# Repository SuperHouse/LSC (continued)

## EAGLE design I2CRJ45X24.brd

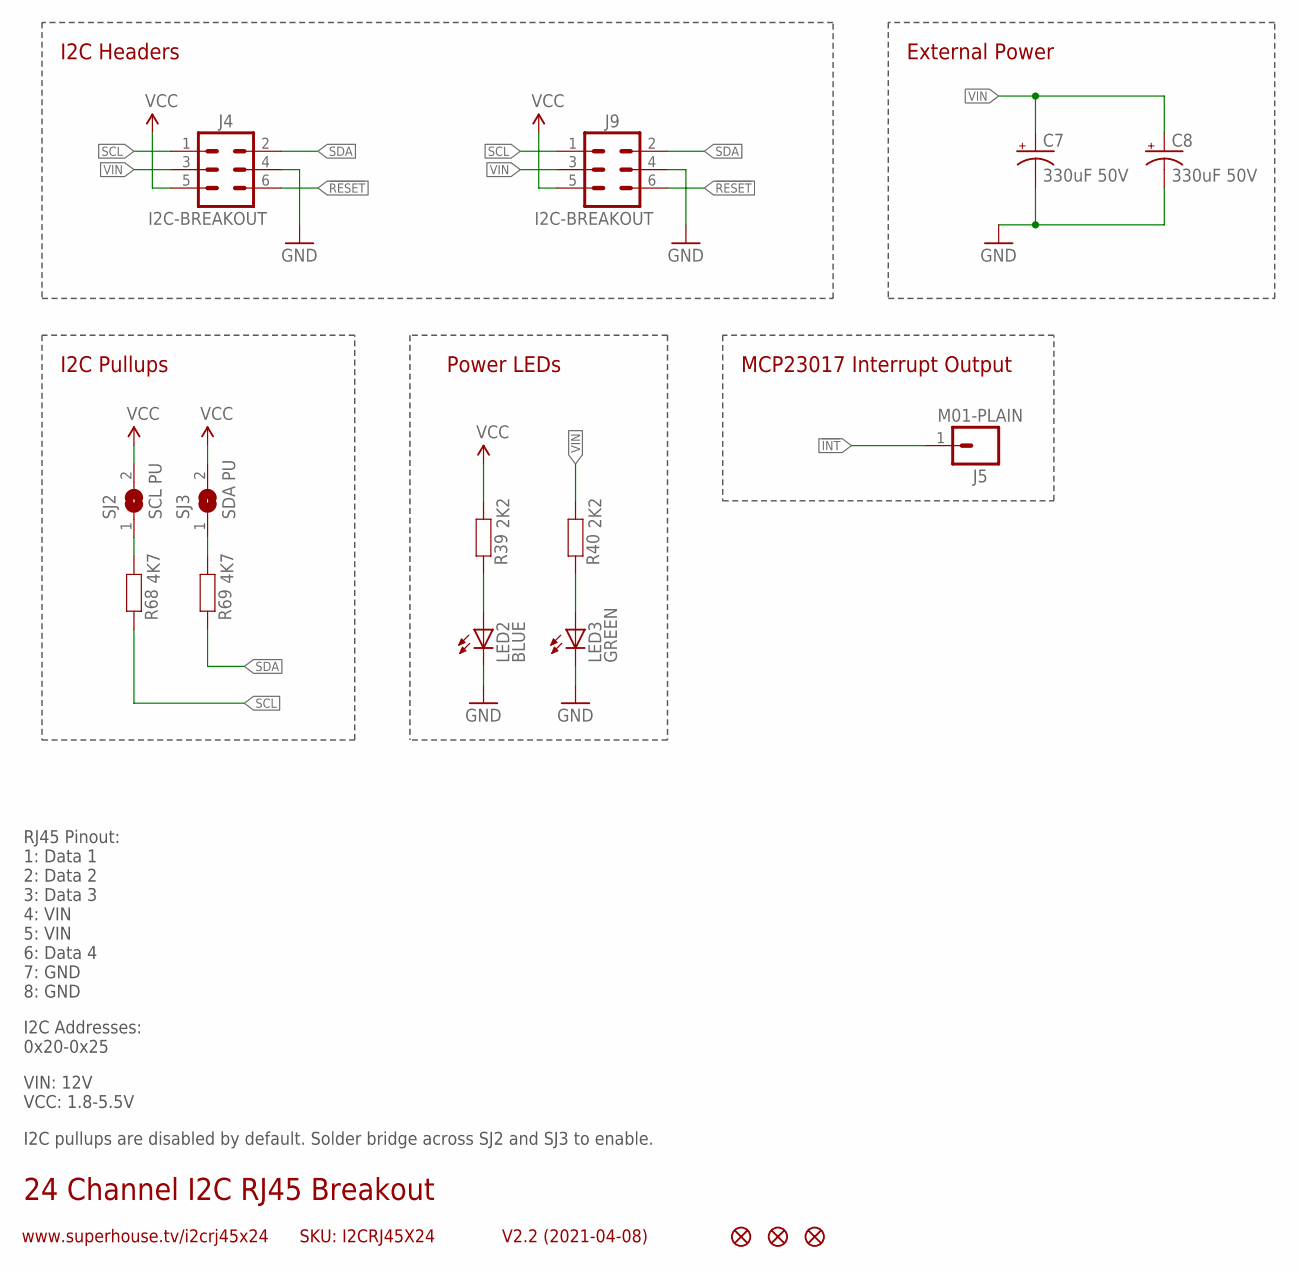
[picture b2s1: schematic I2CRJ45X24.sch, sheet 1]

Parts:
C7, C8: 330uF 50V; PANASONIC_G
FID1, FID2, FID3: FIDUCIAL1X2.5; FIDUCIAL-1X2.5
J4, J9: I2C-BREAKOUT; 2X03-SHROUDED
J5: M01-PLAIN; 1X01
LED2: BLUE; LED-0603
LED3: GREEN; LED-0603
R39, R40: 2K2; R0603
R68, R69: 4K7; R0603
SJ2: SCL PU; SJ
SJ3: SDA PU; SJ

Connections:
!INT: J5.1; also elsewhere on the board
!RESET: J4.6, J9.6; also elsewhere on the board
GND: C7.-, C8.-, J4.4, J9.4, LED2.C, LED3.C; also elsewhere on the board
unnamed: R68.2, SJ2.1
unnamed: R69.2, SJ3.1
unnamed: LED2.A, R39.1
unnamed: LED3.A, R40.1
SCL: J4.1, J9.1, R68.1; also elsewhere on the board
SDA: J4.2, J9.2, R69.1; also elsewhere on the board
VCC: J4.5, J9.5, R39.2, SJ2.2, SJ3.2; also elsewhere on the board
VIN: C7.+, C8.+, J4.3, J9.3, R40.2; also elsewhere on the board

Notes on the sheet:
24 Channel I2C RJ45 Breakout
V2.2 (2021-04-08)
www.superhouse.tv/i2crj45x24
SKU: I2CRJ45X24
RJ45 Pinout: 1: Data 1 2: Data 2 3: Data 3 4: VIN 5: VIN 6: Data 4 7: GND 8: GND
VIN: 12V VCC: 1.8-5.5V
I2C Addresses: 0x20-0x25
External Power
I2C Headers
MCP23017 Interrupt Output
I2C Pullups
I2C pullups are disabled by default. Solder bridge across SJ2 and SJ3 to enable.
Power LEDs

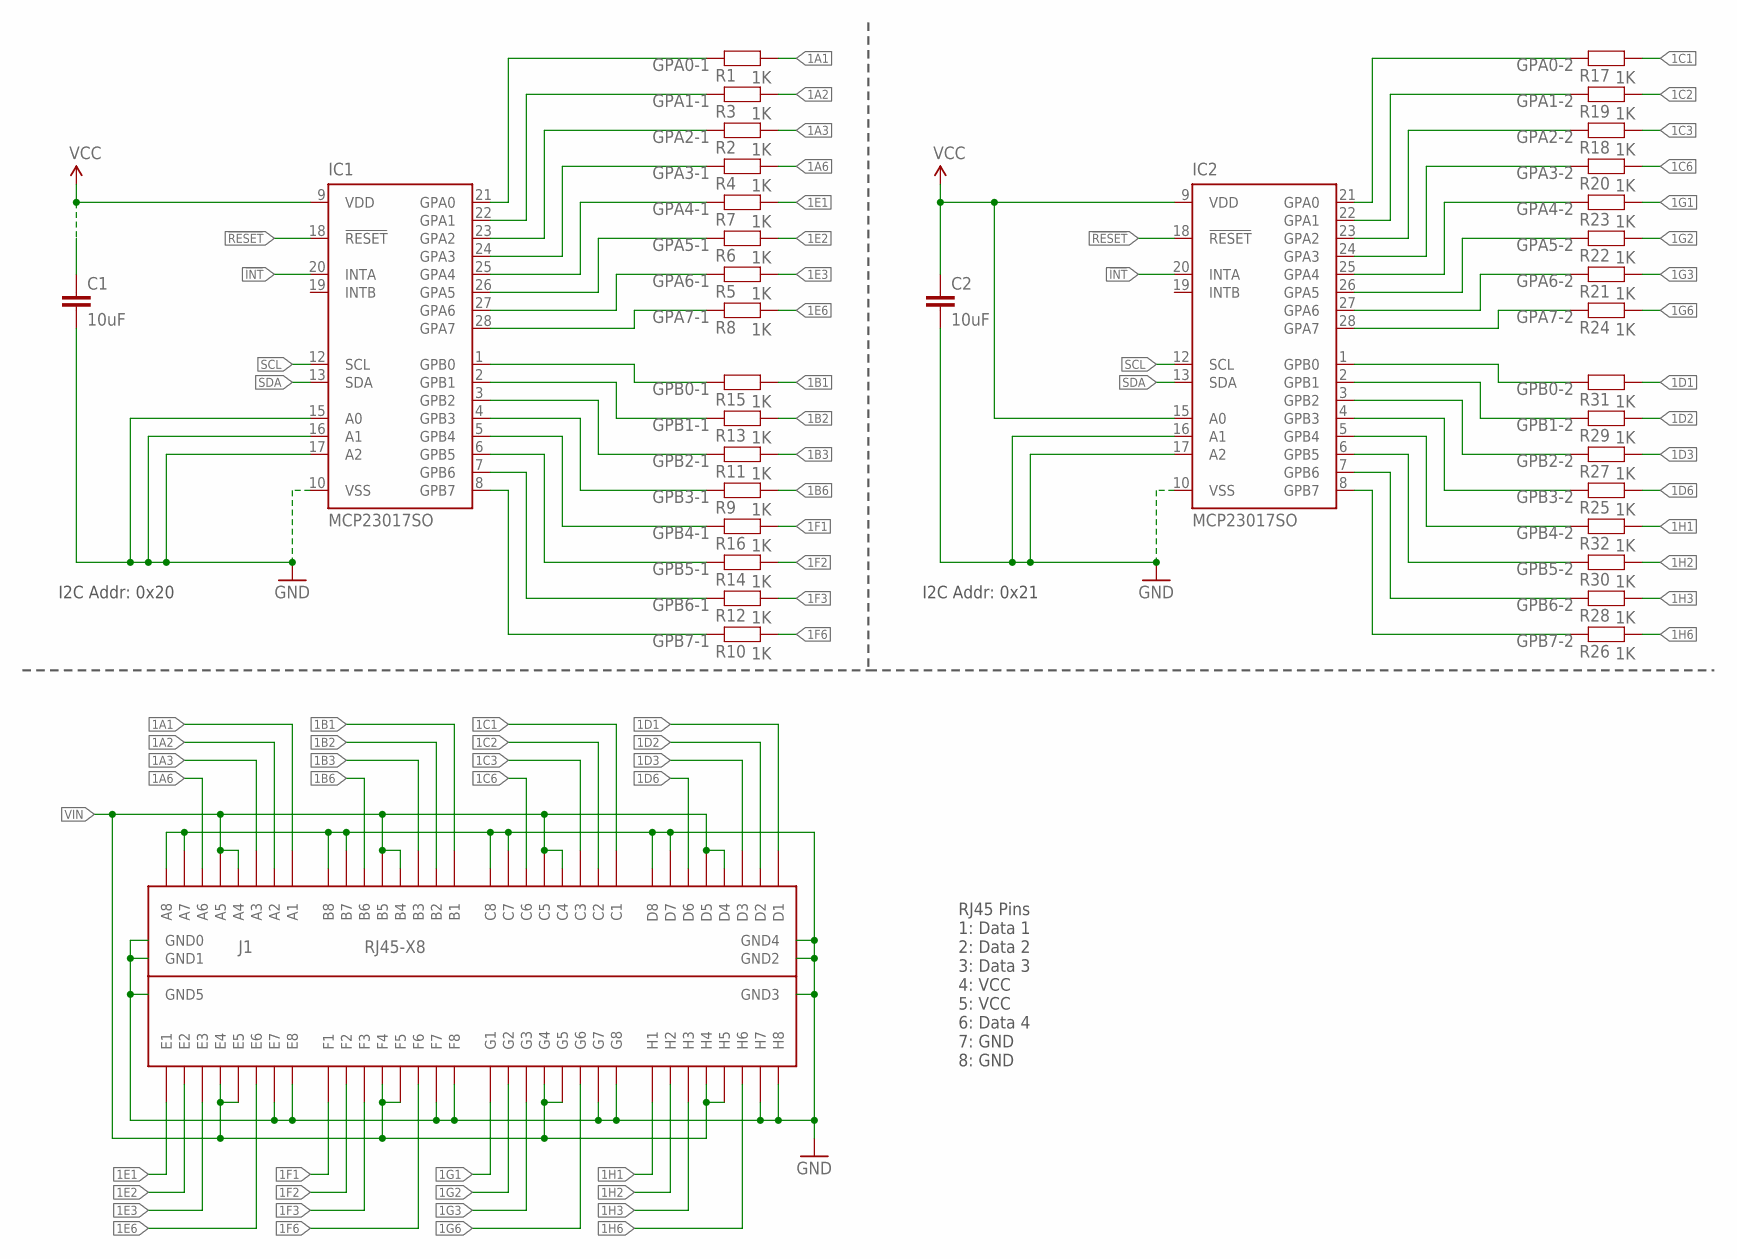
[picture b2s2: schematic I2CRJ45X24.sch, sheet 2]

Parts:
C1, C2: 10uF; C0805
IC1, IC2: MCP23017SO; SO28W
J1: RJ45-X8; RJ45-2X4
R1, R2, R3, R4, R5, R6, R7, R8, R9, R10, R11, R12, R13, R14, R15, R16, R17, R18, R19, R20, R21, R22, R23, R24, R25, R26, R27, R28, R29, R30, R31, R32: 1K; R0603

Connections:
1A1: J1.A1, R1.2
1A2: J1.A2, R3.2
1A3: J1.A3, R2.2
1A6: J1.A6, R4.2
1B1: J1.B1, R15.2
1B2: J1.B2, R13.2
1B3: J1.B3, R11.2
1B6: J1.B6, R9.2
1C1: J1.C1, R17.2
1C2: J1.C2, R19.2
1C3: J1.C3, R18.2
1C6: J1.C6, R20.2
1D1: J1.D1, R31.2
1D2: J1.D2, R29.2
1D3: J1.D3, R27.2
1D6: J1.D6, R25.2
1E1: J1.E1, R7.2
1E2: J1.E2, R6.2
1E3: J1.E3, R5.2
1E6: J1.E6, R8.2
1F1: J1.F1, R16.2
1F2: J1.F2, R14.2
1F3: J1.F3, R12.2
1F6: J1.F6, R10.2
1G1: J1.G1, R23.2
1G2: J1.G2, R22.2
1G3: J1.G3, R21.2
1G6: J1.G6, R24.2
1H1: J1.H1, R32.2
1H2: J1.H2, R30.2
1H3: J1.H3, R28.2
1H6: J1.H6, R26.2
!INT: IC1.20 (INTA), IC2.20 (INTA); also elsewhere on the board
!RESET: IC1.18 (!RESET), IC2.18 (!RESET); also elsewhere on the board
GND: C1.2, C2.2, IC1.10 (VSS), IC1.15 (A0), IC1.16 (A1), IC1.17 (A2), IC2.10 (VSS), IC2.16 (A1), IC2.17 (A2), J1.A7, J1.A8, J1.B7, J1.B8, J1.C7, J1.C8, J1.D7, J1.D8, J1.E7, J1.E8, J1.F7, J1.F8, J1.G7, J1.G8, J1.GND0, J1.GND1, J1.GND2, J1.GND3, J1.GND4, J1.GND5, J1.H7, J1.H8; also elsewhere on the board
GPA0-1: IC1.21 (GPA0), R1.1
GPA0-2: IC2.21 (GPA0), R17.1
GPA1-1: IC1.22 (GPA1), R3.1
GPA1-2: IC2.22 (GPA1), R19.1
GPA2-1: IC1.23 (GPA2), R2.1
GPA2-2: IC2.23 (GPA2), R18.1
GPA3-1: IC1.24 (GPA3), R4.1
GPA3-2: IC2.24 (GPA3), R20.1
GPA4-1: IC1.25 (GPA4), R7.1
GPA4-2: IC2.25 (GPA4), R23.1
GPA5-1: IC1.26 (GPA5), R6.1
GPA5-2: IC2.26 (GPA5), R22.1
GPA6-1: IC1.27 (GPA6), R5.1
GPA6-2: IC2.27 (GPA6), R21.1
GPA7-1: IC1.28 (GPA7), R8.1
GPA7-2: IC2.28 (GPA7), R24.1
GPB0-1: IC1.1 (GPB0), R15.1
GPB0-2: IC2.1 (GPB0), R31.1
GPB1-1: IC1.2 (GPB1), R13.1
GPB1-2: IC2.2 (GPB1), R29.1
GPB2-1: IC1.3 (GPB2), R11.1
GPB2-2: IC2.3 (GPB2), R27.1
GPB3-1: IC1.4 (GPB3), R9.1
GPB3-2: IC2.4 (GPB3), R25.1
GPB4-1: IC1.5 (GPB4), R16.1
GPB4-2: IC2.5 (GPB4), R32.1
GPB5-1: IC1.6 (GPB5), R14.1
GPB5-2: IC2.6 (GPB5), R30.1
GPB6-1: IC1.7 (GPB6), R12.1
GPB6-2: IC2.7 (GPB6), R28.1
GPB7-1: IC1.8 (GPB7), R10.1
GPB7-2: IC2.8 (GPB7), R26.1
SCL: IC1.12 (SCL), IC2.12 (SCL); also elsewhere on the board
SDA: IC1.13 (SDA), IC2.13 (SDA); also elsewhere on the board
VCC: C1.1, C2.1, IC1.9 (VDD), IC2.9 (VDD), IC2.15 (A0); also elsewhere on the board
VIN: J1.A4, J1.A5, J1.B4, J1.B5, J1.C4, J1.C5, J1.D4, J1.D5, J1.E4, J1.E5, J1.F4, J1.F5, J1.G4, J1.G5, J1.H4, J1.H5; also elsewhere on the board

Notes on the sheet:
RJ45 Pins 1: Data 1 2: Data 2 3: Data 3 4: VCC 5: VCC 6: Data 4 7: GND 8: GND
I2C Addr: 0x20
I2C Addr: 0x21

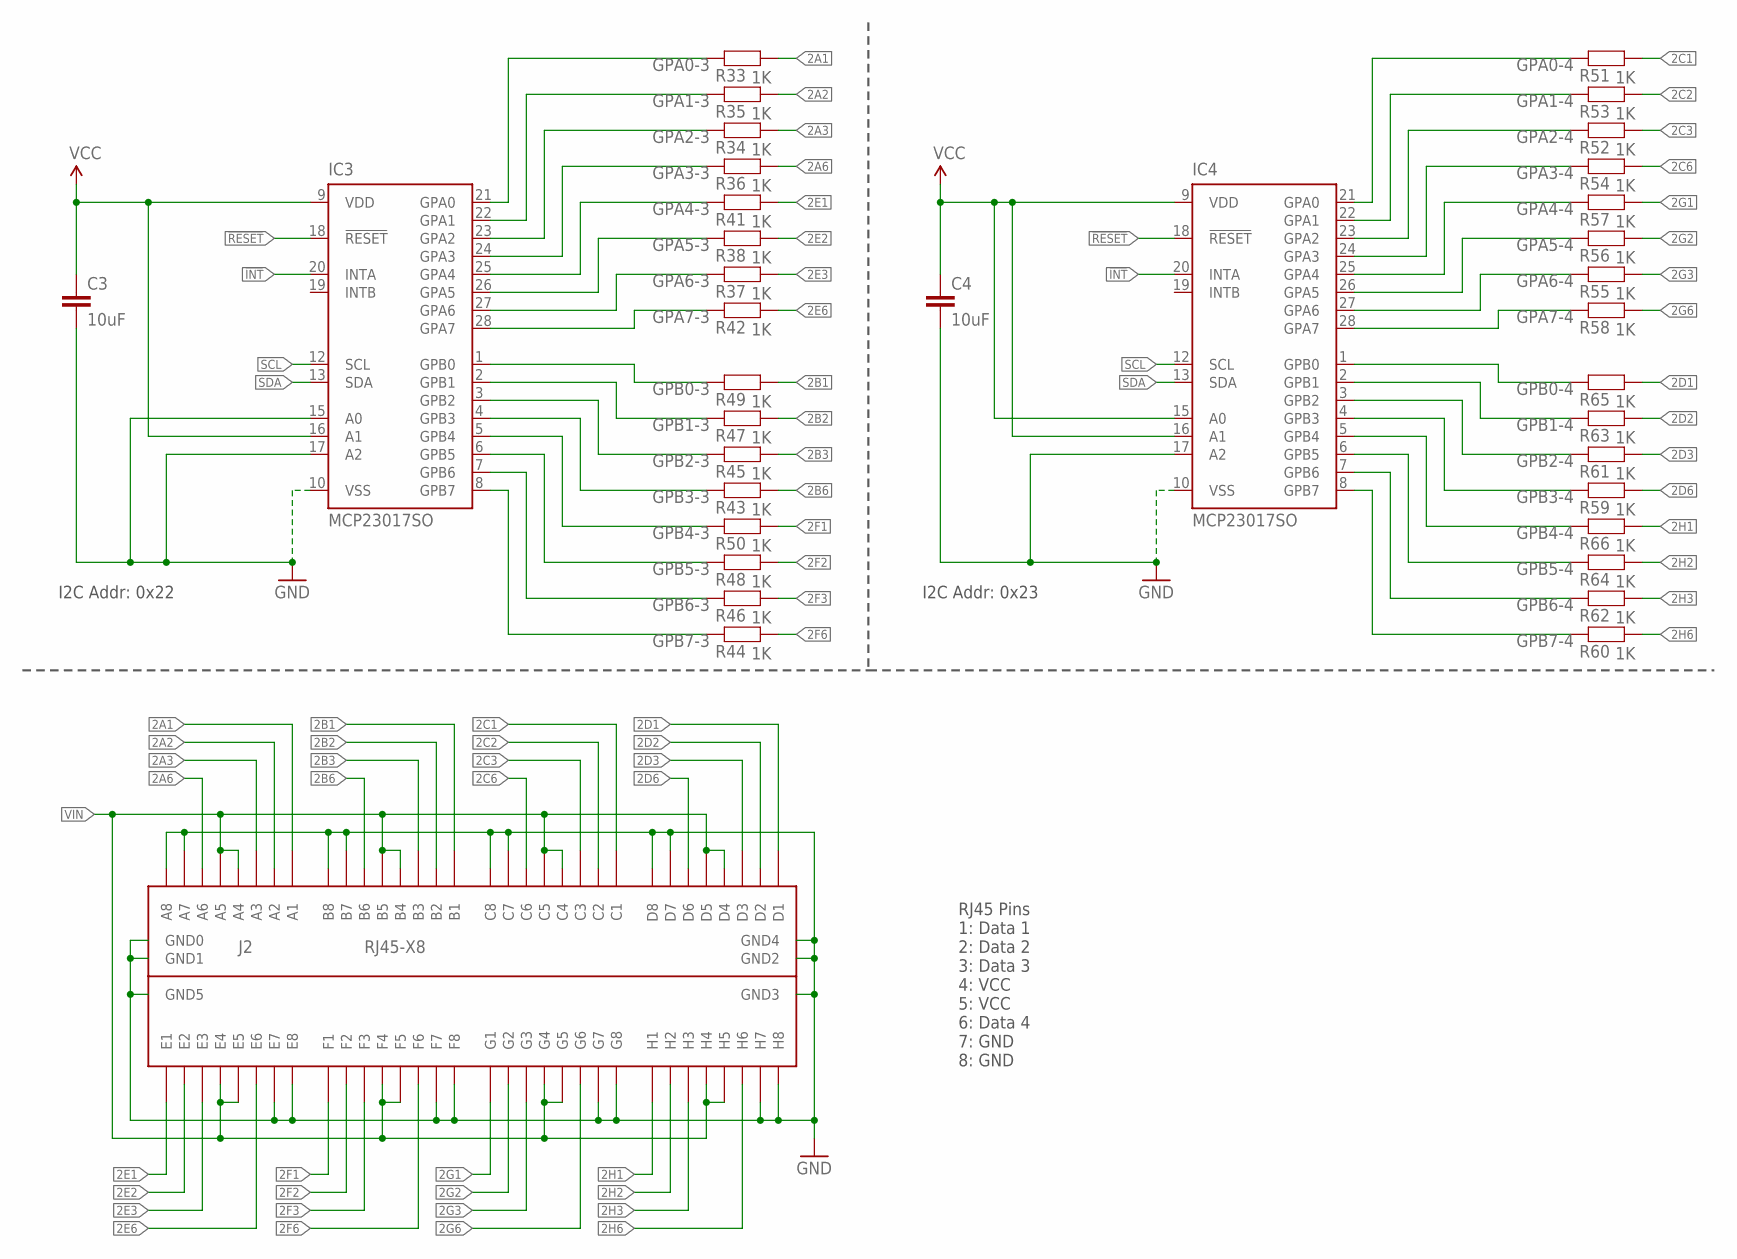
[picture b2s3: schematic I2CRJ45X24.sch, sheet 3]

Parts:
C3, C4: 10uF; C0805
IC3, IC4: MCP23017SO; SO28W
J2: RJ45-X8; RJ45-2X4
R33, R34, R35, R36, R37, R38, R41, R42, R43, R44, R45, R46, R47, R48, R49, R50, R51, R52, R53, R54, R55, R56, R57, R58, R59, R60, R61, R62, R63, R64, R65, R66: 1K; R0603

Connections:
2A1: J2.A1, R33.2
2A2: J2.A2, R35.2
2A3: J2.A3, R34.2
2A6: J2.A6, R36.2
2B1: J2.B1, R49.2
2B2: J2.B2, R47.2
2B3: J2.B3, R45.2
2B6: J2.B6, R43.2
2C1: J2.C1, R51.2
2C2: J2.C2, R53.2
2C3: J2.C3, R52.2
2C6: J2.C6, R54.2
2D1: J2.D1, R65.2
2D2: J2.D2, R63.2
2D3: J2.D3, R61.2
2D6: J2.D6, R59.2
2E1: J2.E1, R41.2
2E2: J2.E2, R38.2
2E3: J2.E3, R37.2
2E6: J2.E6, R42.2
2F1: J2.F1, R50.2
2F2: J2.F2, R48.2
2F3: J2.F3, R46.2
2F6: J2.F6, R44.2
2G1: J2.G1, R57.2
2G2: J2.G2, R56.2
2G3: J2.G3, R55.2
2G6: J2.G6, R58.2
2H1: J2.H1, R66.2
2H2: J2.H2, R64.2
2H3: J2.H3, R62.2
2H6: J2.H6, R60.2
!INT: IC3.20 (INTA), IC4.20 (INTA); also elsewhere on the board
!RESET: IC3.18 (!RESET), IC4.18 (!RESET); also elsewhere on the board
GND: C3.2, C4.2, IC3.10 (VSS), IC3.15 (A0), IC3.17 (A2), IC4.10 (VSS), IC4.17 (A2), J2.A7, J2.A8, J2.B7, J2.B8, J2.C7, J2.C8, J2.D7, J2.D8, J2.E7, J2.E8, J2.F7, J2.F8, J2.G7, J2.G8, J2.GND0, J2.GND1, J2.GND2, J2.GND3, J2.GND4, J2.GND5, J2.H7, J2.H8; also elsewhere on the board
GPA0-3: IC3.21 (GPA0), R33.1
GPA0-4: IC4.21 (GPA0), R51.1
GPA1-3: IC3.22 (GPA1), R35.1
GPA1-4: IC4.22 (GPA1), R53.1
GPA2-3: IC3.23 (GPA2), R34.1
GPA2-4: IC4.23 (GPA2), R52.1
GPA3-3: IC3.24 (GPA3), R36.1
GPA3-4: IC4.24 (GPA3), R54.1
GPA4-3: IC3.25 (GPA4), R41.1
GPA4-4: IC4.25 (GPA4), R57.1
GPA5-3: IC3.26 (GPA5), R38.1
GPA5-4: IC4.26 (GPA5), R56.1
GPA6-3: IC3.27 (GPA6), R37.1
GPA6-4: IC4.27 (GPA6), R55.1
GPA7-3: IC3.28 (GPA7), R42.1
GPA7-4: IC4.28 (GPA7), R58.1
GPB0-3: IC3.1 (GPB0), R49.1
GPB0-4: IC4.1 (GPB0), R65.1
GPB1-3: IC3.2 (GPB1), R47.1
GPB1-4: IC4.2 (GPB1), R63.1
GPB2-3: IC3.3 (GPB2), R45.1
GPB2-4: IC4.3 (GPB2), R61.1
GPB3-3: IC3.4 (GPB3), R43.1
GPB3-4: IC4.4 (GPB3), R59.1
GPB4-3: IC3.5 (GPB4), R50.1
GPB4-4: IC4.5 (GPB4), R66.1
GPB5-3: IC3.6 (GPB5), R48.1
GPB5-4: IC4.6 (GPB5), R64.1
GPB6-3: IC3.7 (GPB6), R46.1
GPB6-4: IC4.7 (GPB6), R62.1
GPB7-3: IC3.8 (GPB7), R44.1
GPB7-4: IC4.8 (GPB7), R60.1
SCL: IC3.12 (SCL), IC4.12 (SCL); also elsewhere on the board
SDA: IC3.13 (SDA), IC4.13 (SDA); also elsewhere on the board
VCC: C3.1, C4.1, IC3.9 (VDD), IC3.16 (A1), IC4.9 (VDD), IC4.15 (A0), IC4.16 (A1); also elsewhere on the board
VIN: J2.A4, J2.A5, J2.B4, J2.B5, J2.C4, J2.C5, J2.D4, J2.D5, J2.E4, J2.E5, J2.F4, J2.F5, J2.G4, J2.G5, J2.H4, J2.H5; also elsewhere on the board

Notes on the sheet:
RJ45 Pins 1: Data 1 2: Data 2 3: Data 3 4: VCC 5: VCC 6: Data 4 7: GND 8: GND
I2C Addr: 0x22
I2C Addr: 0x23

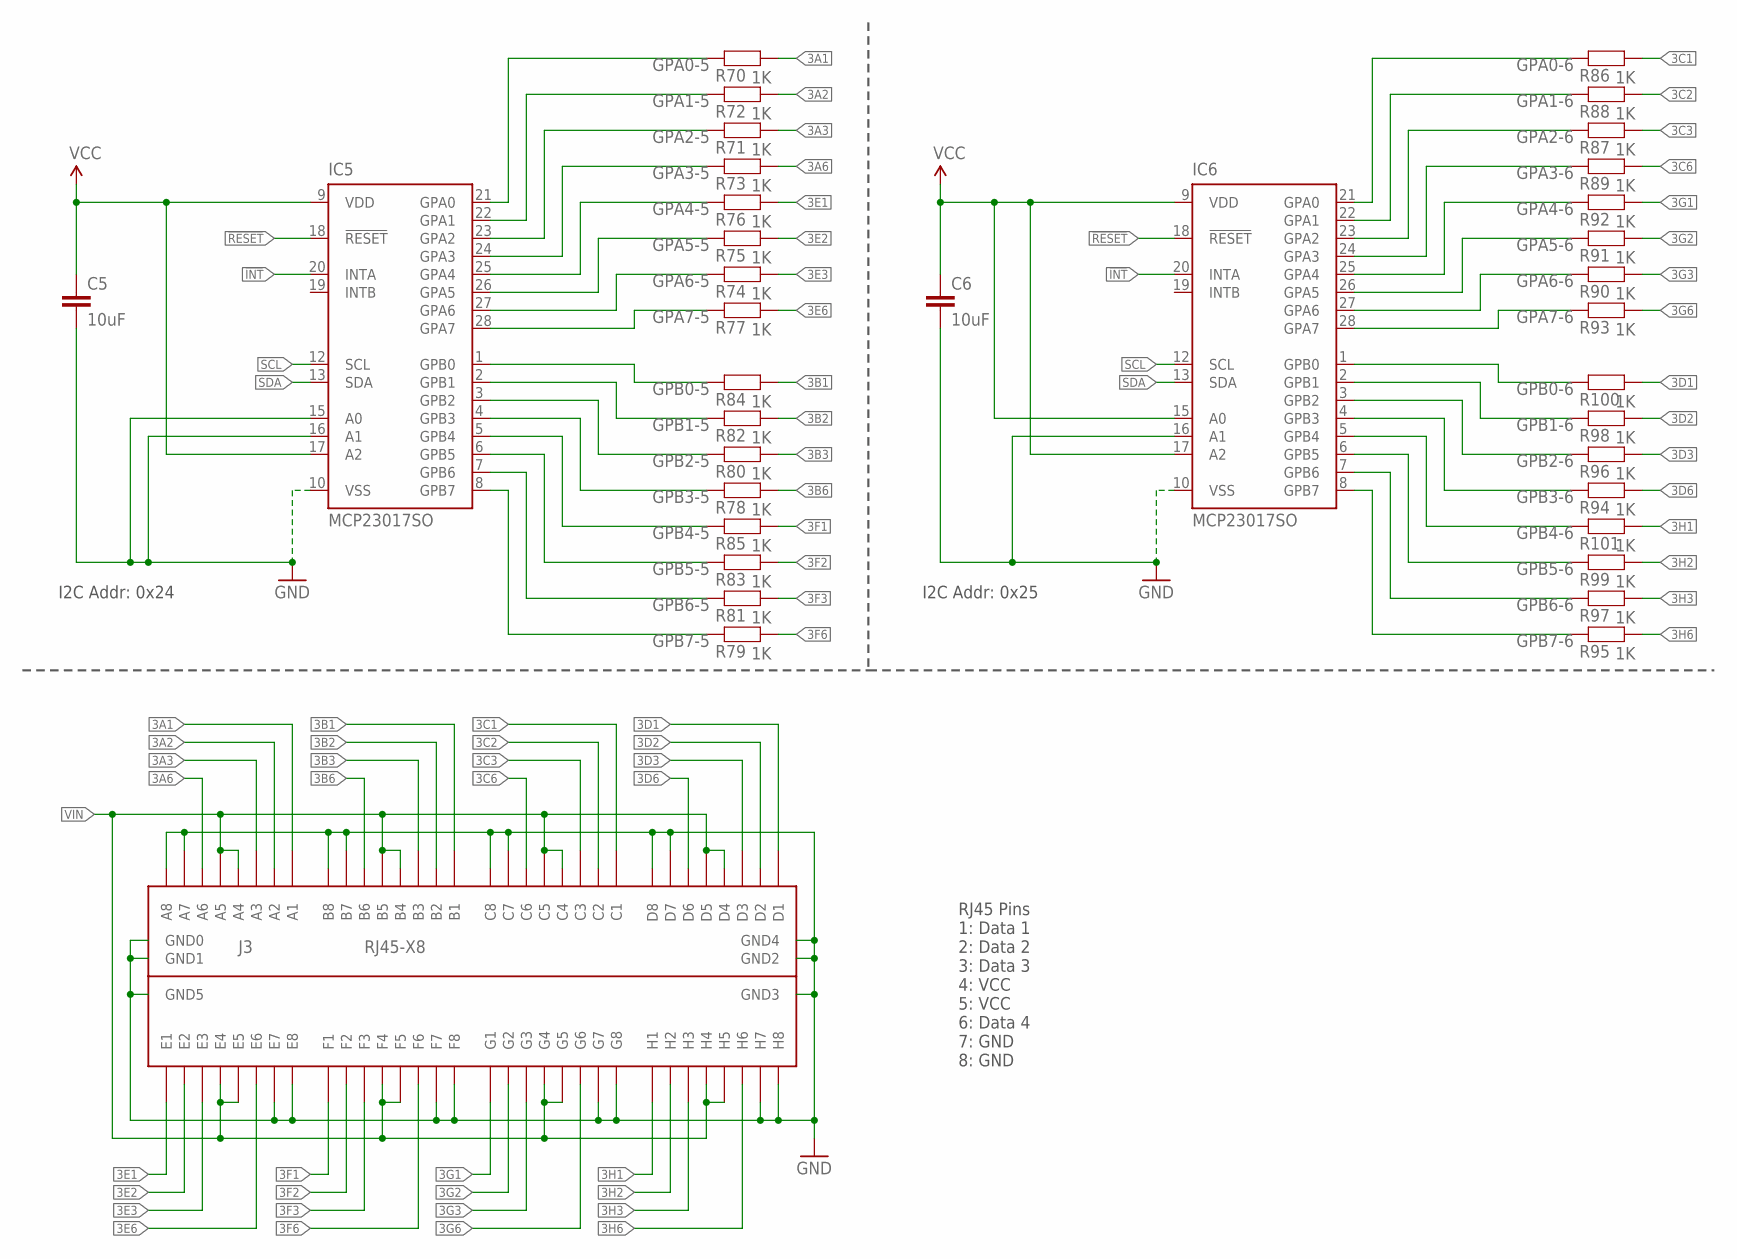
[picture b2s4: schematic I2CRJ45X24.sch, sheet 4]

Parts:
C5, C6: 10uF; C0805
IC5, IC6: MCP23017SO; SO28W
J3: RJ45-X8; RJ45-2X4
R70, R71, R72, R73, R74, R75, R76, R77, R78, R79, R80, R81, R82, R83, R84, R85, R86, R87, R88, R89, R90, R91, R92, R93, R94, R95, R96, R97, R98, R99, R100, R101: 1K; R0603

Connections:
3A1: J3.A1, R70.2
3A2: J3.A2, R72.2
3A3: J3.A3, R71.2
3A6: J3.A6, R73.2
3B1: J3.B1, R84.2
3B2: J3.B2, R82.2
3B3: J3.B3, R80.2
3B6: J3.B6, R78.2
3C1: J3.C1, R86.2
3C2: J3.C2, R88.2
3C3: J3.C3, R87.2
3C6: J3.C6, R89.2
3D1: J3.D1, R100.2
3D2: J3.D2, R98.2
3D3: J3.D3, R96.2
3D6: J3.D6, R94.2
3E1: J3.E1, R76.2
3E2: J3.E2, R75.2
3E3: J3.E3, R74.2
3E6: J3.E6, R77.2
3F1: J3.F1, R85.2
3F2: J3.F2, R83.2
3F3: J3.F3, R81.2
3F6: J3.F6, R79.2
3G1: J3.G1, R92.2
3G2: J3.G2, R91.2
3G3: J3.G3, R90.2
3G6: J3.G6, R93.2
3H1: J3.H1, R101.2
3H2: J3.H2, R99.2
3H3: J3.H3, R97.2
3H6: J3.H6, R95.2
!INT: IC5.20 (INTA), IC6.20 (INTA); also elsewhere on the board
!RESET: IC5.18 (!RESET), IC6.18 (!RESET); also elsewhere on the board
GND: C5.2, C6.2, IC5.10 (VSS), IC5.15 (A0), IC5.16 (A1), IC6.10 (VSS), IC6.16 (A1), J3.A7, J3.A8, J3.B7, J3.B8, J3.C7, J3.C8, J3.D7, J3.D8, J3.E7, J3.E8, J3.F7, J3.F8, J3.G7, J3.G8, J3.GND0, J3.GND1, J3.GND2, J3.GND3, J3.GND4, J3.GND5, J3.H7, J3.H8; also elsewhere on the board
GPA0-5: IC5.21 (GPA0), R70.1
GPA0-6: IC6.21 (GPA0), R86.1
GPA1-5: IC5.22 (GPA1), R72.1
GPA1-6: IC6.22 (GPA1), R88.1
GPA2-5: IC5.23 (GPA2), R71.1
GPA2-6: IC6.23 (GPA2), R87.1
GPA3-5: IC5.24 (GPA3), R73.1
GPA3-6: IC6.24 (GPA3), R89.1
GPA4-5: IC5.25 (GPA4), R76.1
GPA4-6: IC6.25 (GPA4), R92.1
GPA5-5: IC5.26 (GPA5), R75.1
GPA5-6: IC6.26 (GPA5), R91.1
GPA6-5: IC5.27 (GPA6), R74.1
GPA6-6: IC6.27 (GPA6), R90.1
GPA7-5: IC5.28 (GPA7), R77.1
GPA7-6: IC6.28 (GPA7), R93.1
GPB0-5: IC5.1 (GPB0), R84.1
GPB0-6: IC6.1 (GPB0), R100.1
GPB1-5: IC5.2 (GPB1), R82.1
GPB1-6: IC6.2 (GPB1), R98.1
GPB2-5: IC5.3 (GPB2), R80.1
GPB2-6: IC6.3 (GPB2), R96.1
GPB3-5: IC5.4 (GPB3), R78.1
GPB3-6: IC6.4 (GPB3), R94.1
GPB4-5: IC5.5 (GPB4), R85.1
GPB4-6: IC6.5 (GPB4), R101.1
GPB5-5: IC5.6 (GPB5), R83.1
GPB5-6: IC6.6 (GPB5), R99.1
GPB6-5: IC5.7 (GPB6), R81.1
GPB6-6: IC6.7 (GPB6), R97.1
GPB7-5: IC5.8 (GPB7), R79.1
GPB7-6: IC6.8 (GPB7), R95.1
SCL: IC5.12 (SCL), IC6.12 (SCL); also elsewhere on the board
SDA: IC5.13 (SDA), IC6.13 (SDA); also elsewhere on the board
VCC: C5.1, C6.1, IC5.9 (VDD), IC5.17 (A2), IC6.9 (VDD), IC6.15 (A0), IC6.17 (A2); also elsewhere on the board
VIN: J3.A4, J3.A5, J3.B4, J3.B5, J3.C4, J3.C5, J3.D4, J3.D5, J3.E4, J3.E5, J3.F4, J3.F5, J3.G4, J3.G5, J3.H4, J3.H5; also elsewhere on the board

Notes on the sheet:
RJ45 Pins 1: Data 1 2: Data 2 3: Data 3 4: VCC 5: VCC 6: Data 4 7: GND 8: GND
I2C Addr: 0x24
I2C Addr: 0x25

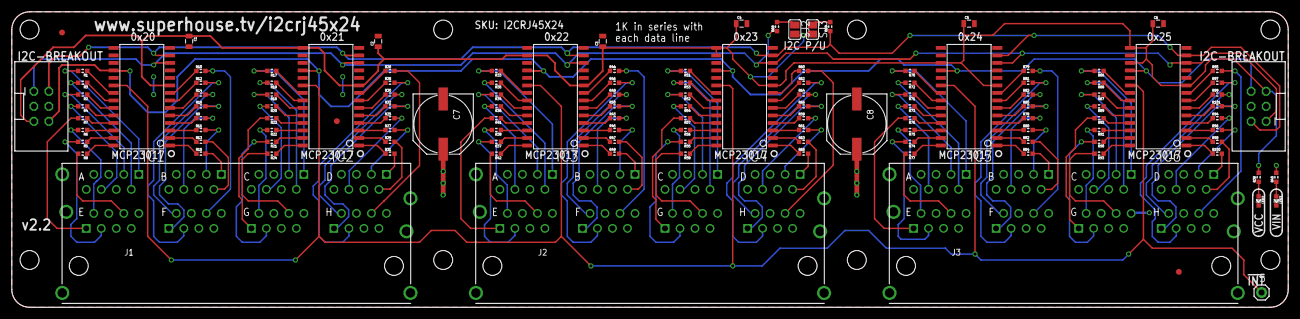
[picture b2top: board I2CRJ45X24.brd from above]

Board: 2 copper layers, 216.0 x 50.0 mm, 127 parts (0 on the bottom side), 203 nets.

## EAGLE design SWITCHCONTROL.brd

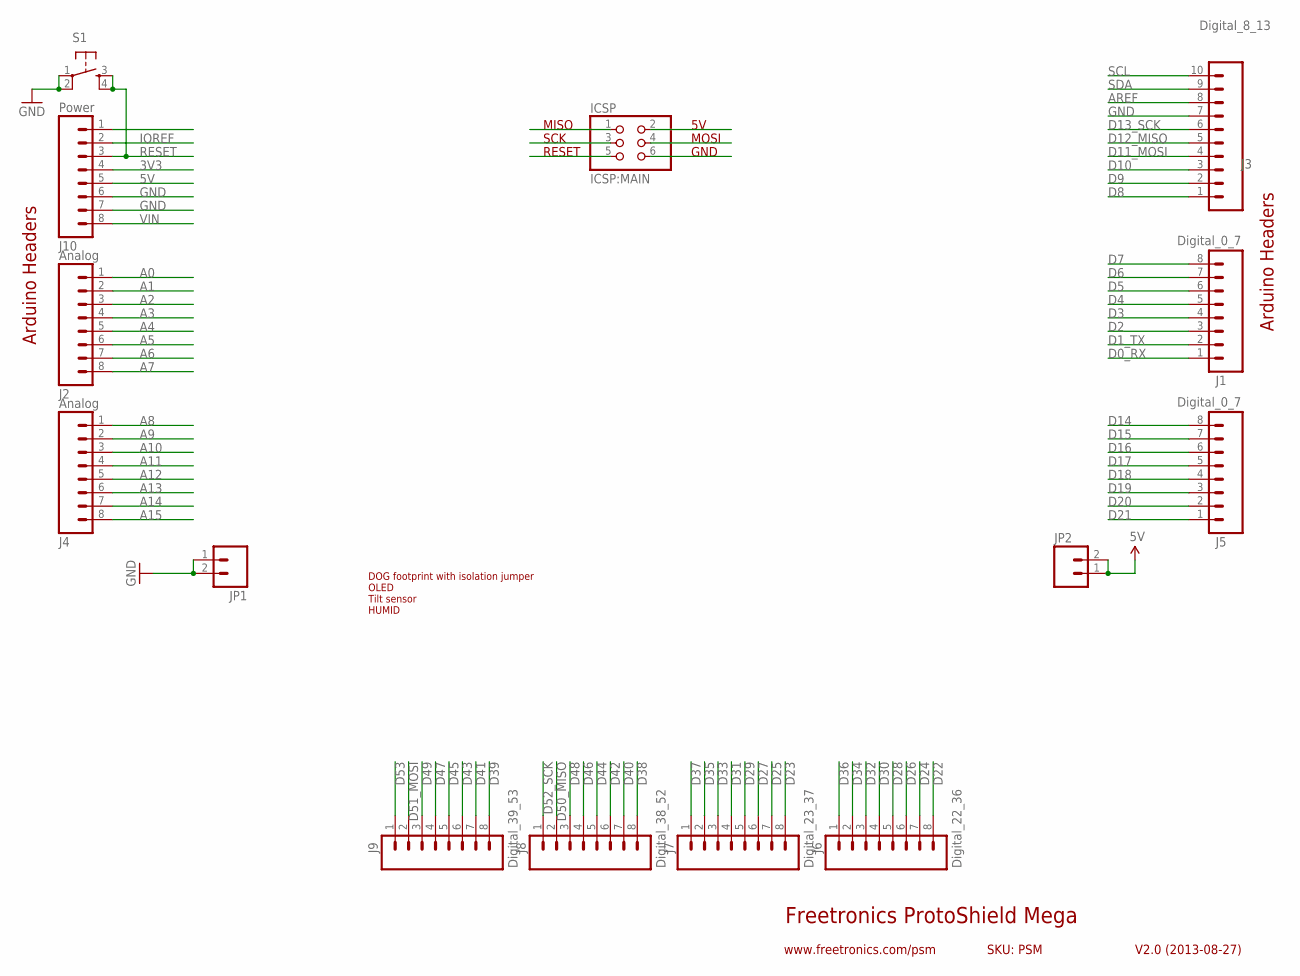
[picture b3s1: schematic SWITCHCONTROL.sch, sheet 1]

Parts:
ICSP: ICSP:MAIN; 2X03
J1, J5: Digital_0_7; 1X08
J2, J4: Analog; 1X08
J3: Digital_8_13; 1X10
J6: Digital_22_36; 1X08
J7: Digital_23_37; 1X08
J8: Digital_38_52; 1X08
J9: Digital_39_53; 1X08
J10: Power; 1X08
JP1, JP2: M02PTH; 1X02
S1: TAC_SWITCHPTH; TACTILE-PTH

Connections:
3V3: J10.4
5V: J10.5, JP2.1, JP2.2
A0: J2.1; also elsewhere on the board
A1: J2.2; also elsewhere on the board
A2: J2.3; also elsewhere on the board
A3: J2.4; also elsewhere on the board
A4: J2.5; also elsewhere on the board
A5: J2.6; also elsewhere on the board
A6: J2.7; also elsewhere on the board
A7: J2.8; also elsewhere on the board
A8: J4.1; also elsewhere on the board
A9: J4.2; also elsewhere on the board
A10: J4.3; also elsewhere on the board
A11: J4.4; also elsewhere on the board
A12: J4.5; also elsewhere on the board
A13: J4.6; also elsewhere on the board
A14: J4.7; also elsewhere on the board
A15: J4.8; also elsewhere on the board
AREF: J3.8
D0_RX: J1.1
D1_TX: J1.2
D2: J1.3
D3: J1.4
D4: J1.5
D5: J1.6
D6: J1.7
D7: J1.8
D8: J3.1
D9: J3.2
D10: J3.3
D11_MOSI: J3.4
D12_MISO: J3.5
D13_SCK: J3.6
D14: J5.8
D15: J5.7
D16: J5.6; also elsewhere on the board
D17: J5.5; also elsewhere on the board
D18: J5.4; also elsewhere on the board
D19: J5.3; also elsewhere on the board
D20: J5.2; also elsewhere on the board
D21: J5.1; also elsewhere on the board
D22: J6.8; also elsewhere on the board
D23: J7.8; also elsewhere on the board
D24: J6.7; also elsewhere on the board
D25: J7.7; also elsewhere on the board
D26: J6.6; also elsewhere on the board
D27: J7.6; also elsewhere on the board
D28: J6.5; also elsewhere on the board
D29: J7.5; also elsewhere on the board
D30: J6.4; also elsewhere on the board
D31: J7.4; also elsewhere on the board
D32: J6.3; also elsewhere on the board
D33: J7.3; also elsewhere on the board
D34: J6.2; also elsewhere on the board
D35: J7.2; also elsewhere on the board
D36: J6.1; also elsewhere on the board
D37: J7.1; also elsewhere on the board
D38: J8.8; also elsewhere on the board
D39: J9.8; also elsewhere on the board
D40: J8.7; also elsewhere on the board
D41: J9.7; also elsewhere on the board
D42: J8.6; also elsewhere on the board
D43: J9.6; also elsewhere on the board
D44: J8.5; also elsewhere on the board
D45: J9.5; also elsewhere on the board
D46: J8.4; also elsewhere on the board
D47: J9.4; also elsewhere on the board
D48: J8.3
D49: J9.3
D50_MISO: J8.2
D51_MOSI: J9.2
D52_SCK: J8.1
D53: J9.1
GND: J3.7, J10.6, J10.7, JP1.1, JP1.2, S1.1, S1.2; also elsewhere on the board
IOREF: J10.2
RESET: J10.3, S1.3, S1.4
SCL: J3.10
SDA: J3.9
VIN: J10.8; also elsewhere on the board

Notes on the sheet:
Freetronics ProtoShield Mega
V2.0 (2013-08-27)
www.freetronics.com/psm
SKU: PSM
Arduino Headers
GND
MISO
RESET
SCK
MOSI
DOG footprint with isolation jumper OLED Tilt sensor HUMID

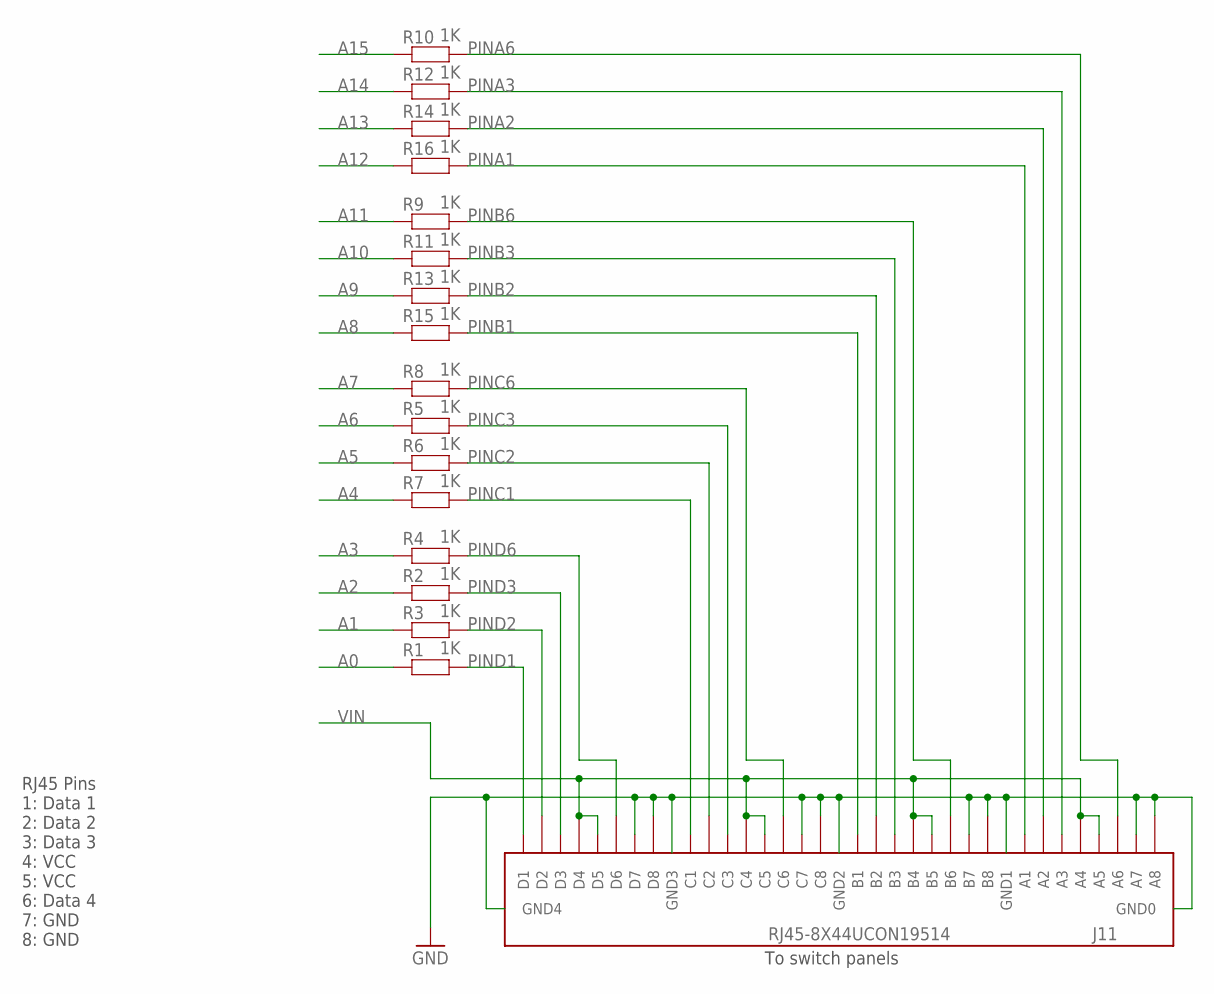
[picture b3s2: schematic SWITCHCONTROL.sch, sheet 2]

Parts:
J11: RJ45-8X44UCON19514; RJ45-8X4
R1, R2, R3, R4, R5, R6, R7, R8, R9, R10, R11, R12, R13, R14, R15, R16: 1K; 0603

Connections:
A0: R1.1; also elsewhere on the board
A1: R3.1; also elsewhere on the board
A2: R2.1; also elsewhere on the board
A3: R4.1; also elsewhere on the board
A4: R7.1; also elsewhere on the board
A5: R6.1; also elsewhere on the board
A6: R5.1; also elsewhere on the board
A7: R8.1; also elsewhere on the board
A8: R15.1; also elsewhere on the board
A9: R13.1; also elsewhere on the board
A10: R11.1; also elsewhere on the board
A11: R9.1; also elsewhere on the board
A12: R16.1; also elsewhere on the board
A13: R14.1; also elsewhere on the board
A14: R12.1; also elsewhere on the board
A15: R10.1; also elsewhere on the board
GND: J11.A7, J11.A8, J11.B7, J11.B8, J11.C7, J11.C8, J11.D7, J11.D8, J11.GND0, J11.GND1, J11.GND2, J11.GND3, J11.GND4; also elsewhere on the board
PINA1: J11.A1, R16.2
PINA2: J11.A2, R14.2
PINA3: J11.A3, R12.2
PINA6: J11.A6, R10.2
PINB1: J11.B1, R15.2
PINB2: J11.B2, R13.2
PINB3: J11.B3, R11.2
PINB6: J11.B6, R9.2
PINC1: J11.C1, R7.2
PINC2: J11.C2, R6.2
PINC3: J11.C3, R5.2
PINC6: J11.C6, R8.2
PIND1: J11.D1, R1.2
PIND2: J11.D2, R3.2
PIND3: J11.D3, R2.2
PIND6: J11.D6, R4.2
VIN: J11.A4, J11.A5, J11.B4, J11.B5, J11.C4, J11.C5, J11.D4, J11.D5; also elsewhere on the board

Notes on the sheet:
To switch panels
RJ45 Pins 1: Data 1 2: Data 2 3: Data 3 4: VCC 5: VCC 6: Data 4 7: GND 8: GND

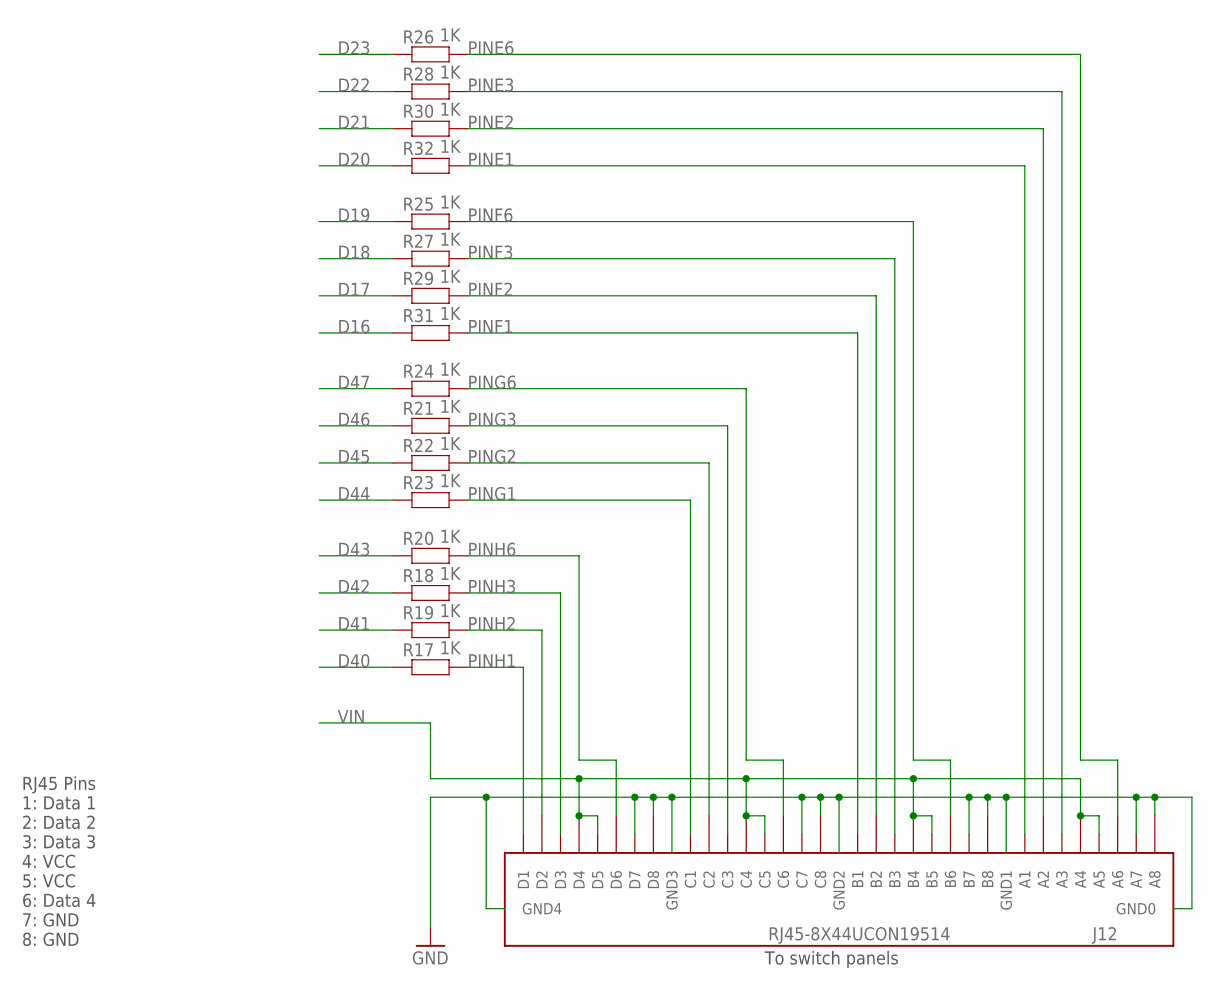
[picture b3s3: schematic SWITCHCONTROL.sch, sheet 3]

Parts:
J12: RJ45-8X44UCON19514; RJ45-8X4
R17, R18, R19, R20, R21, R22, R23, R24, R25, R26, R27, R28, R29, R30, R31, R32: 1K; 0603

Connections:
D16: R31.1; also elsewhere on the board
D17: R29.1; also elsewhere on the board
D18: R27.1; also elsewhere on the board
D19: R25.1; also elsewhere on the board
D20: R32.1; also elsewhere on the board
D21: R30.1; also elsewhere on the board
D22: R28.1; also elsewhere on the board
D23: R26.1; also elsewhere on the board
D40: R17.1; also elsewhere on the board
D41: R19.1; also elsewhere on the board
D42: R18.1; also elsewhere on the board
D43: R20.1; also elsewhere on the board
D44: R23.1; also elsewhere on the board
D45: R22.1; also elsewhere on the board
D46: R21.1; also elsewhere on the board
D47: R24.1; also elsewhere on the board
GND: J12.A7, J12.A8, J12.B7, J12.B8, J12.C7, J12.C8, J12.D7, J12.D8, J12.GND0, J12.GND1, J12.GND2, J12.GND3, J12.GND4; also elsewhere on the board
PINE1: J12.A1, R32.2
PINE2: J12.A2, R30.2
PINE3: J12.A3, R28.2
PINE6: J12.A6, R26.2
PINF1: J12.B1, R31.2
PINF2: J12.B2, R29.2
PINF3: J12.B3, R27.2
PINF6: J12.B6, R25.2
PING1: J12.C1, R23.2
PING2: J12.C2, R22.2
PING3: J12.C3, R21.2
PING6: J12.C6, R24.2
PINH1: J12.D1, R17.2
PINH2: J12.D2, R19.2
PINH3: J12.D3, R18.2
PINH6: J12.D6, R20.2
VIN: J12.A4, J12.A5, J12.B4, J12.B5, J12.C4, J12.C5, J12.D4, J12.D5; also elsewhere on the board

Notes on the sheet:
To switch panels
RJ45 Pins 1: Data 1 2: Data 2 3: Data 3 4: VCC 5: VCC 6: Data 4 7: GND 8: GND

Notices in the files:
I2CRJ45X24.brd:
Copyright 2019-2021 SuperHouse Automation Pty Ltd
License: www.tapr.org/OHL
SWITCHCONTROL.brd:
(C)2017 SuperHouse Automation Pty Ltd
